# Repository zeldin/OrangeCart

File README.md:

The Orange Cartridge -- an FPGA cartridge for the C64/C128
==========================================================

This is an open source hardware FPGA cartridge for the C64 and C128.
The main features are:
 * ECP5 FPGA with 24k LUTs and 126 KB of block RAM
 * 16 MB of HyperRAM
 * 16 MB of SPI NOR Flash
 * Full speed USB
 * Micro SD-card
 * RGB LED
 * Pushbutton

Usage
-----

For full usage instructions and other detailed information, please refer to
[the wiki][wiki].

The cartridge can be powered from the expansion port, from the USB connector,
or both at once (back-current protection diodes are present at each power
input).

To enter the bootloader, keep the pushbutton pressed down when applying
power.  The LED will start flashing in a rainbow pattern.  A new bitstream
can now be uploaded using DFU.

Example bitstreams
------------------

- [RVCop64](https://github.com/zeldin/RVCop64)
- [super-reu](https://github.com/zeldin/super-reu)

[wiki]: https://github.com/zeldin/OrangeCart/wiki

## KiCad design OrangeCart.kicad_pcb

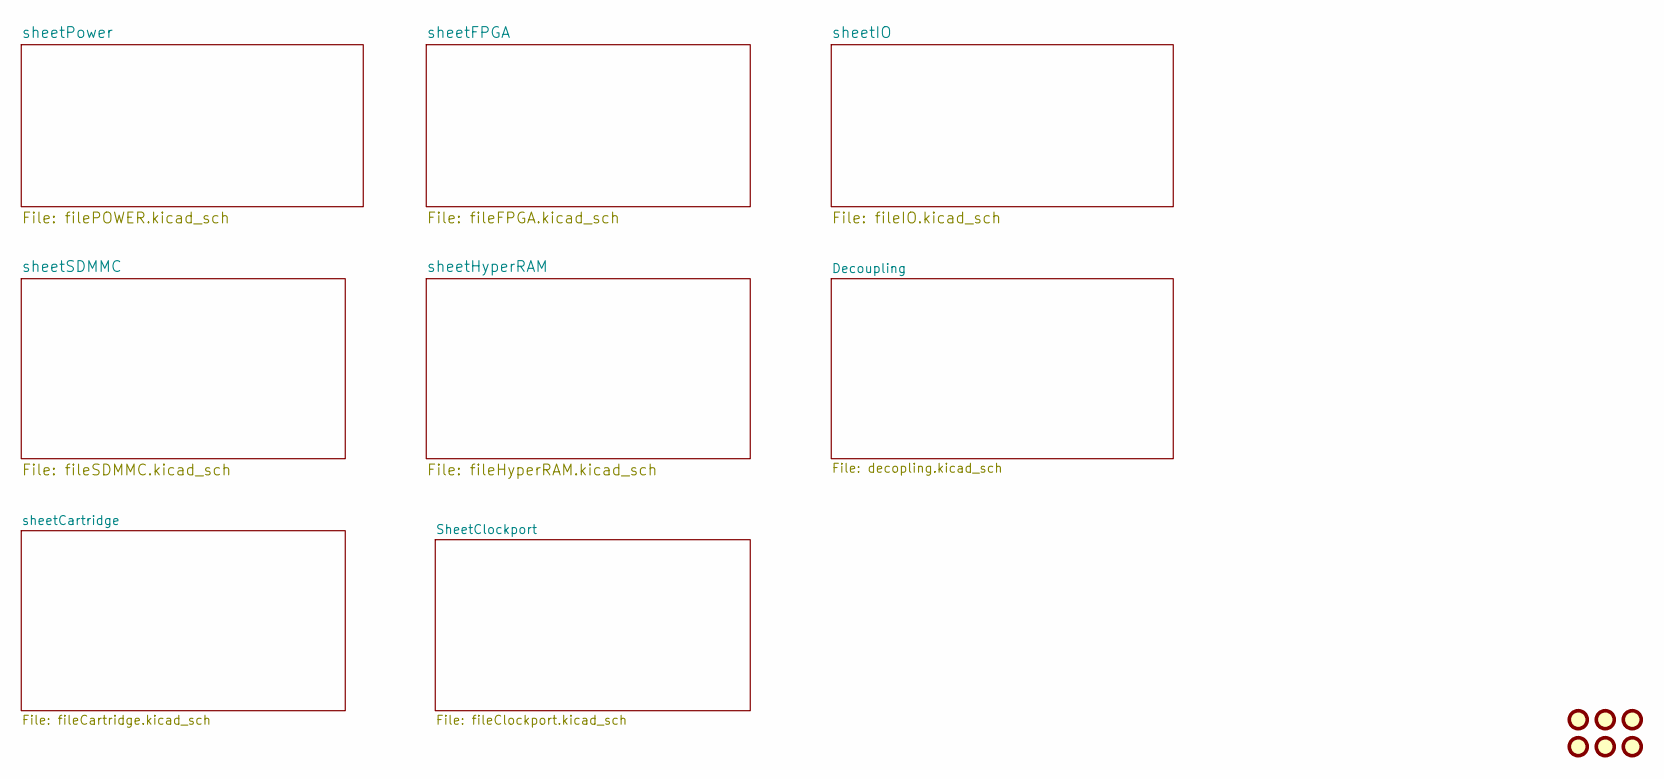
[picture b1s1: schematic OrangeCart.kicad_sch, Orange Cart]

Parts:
FID1, FID2, FID3, FID4, FID5, FID6: Fiducial; Fiducial_0.75mm_Mask1.5mm

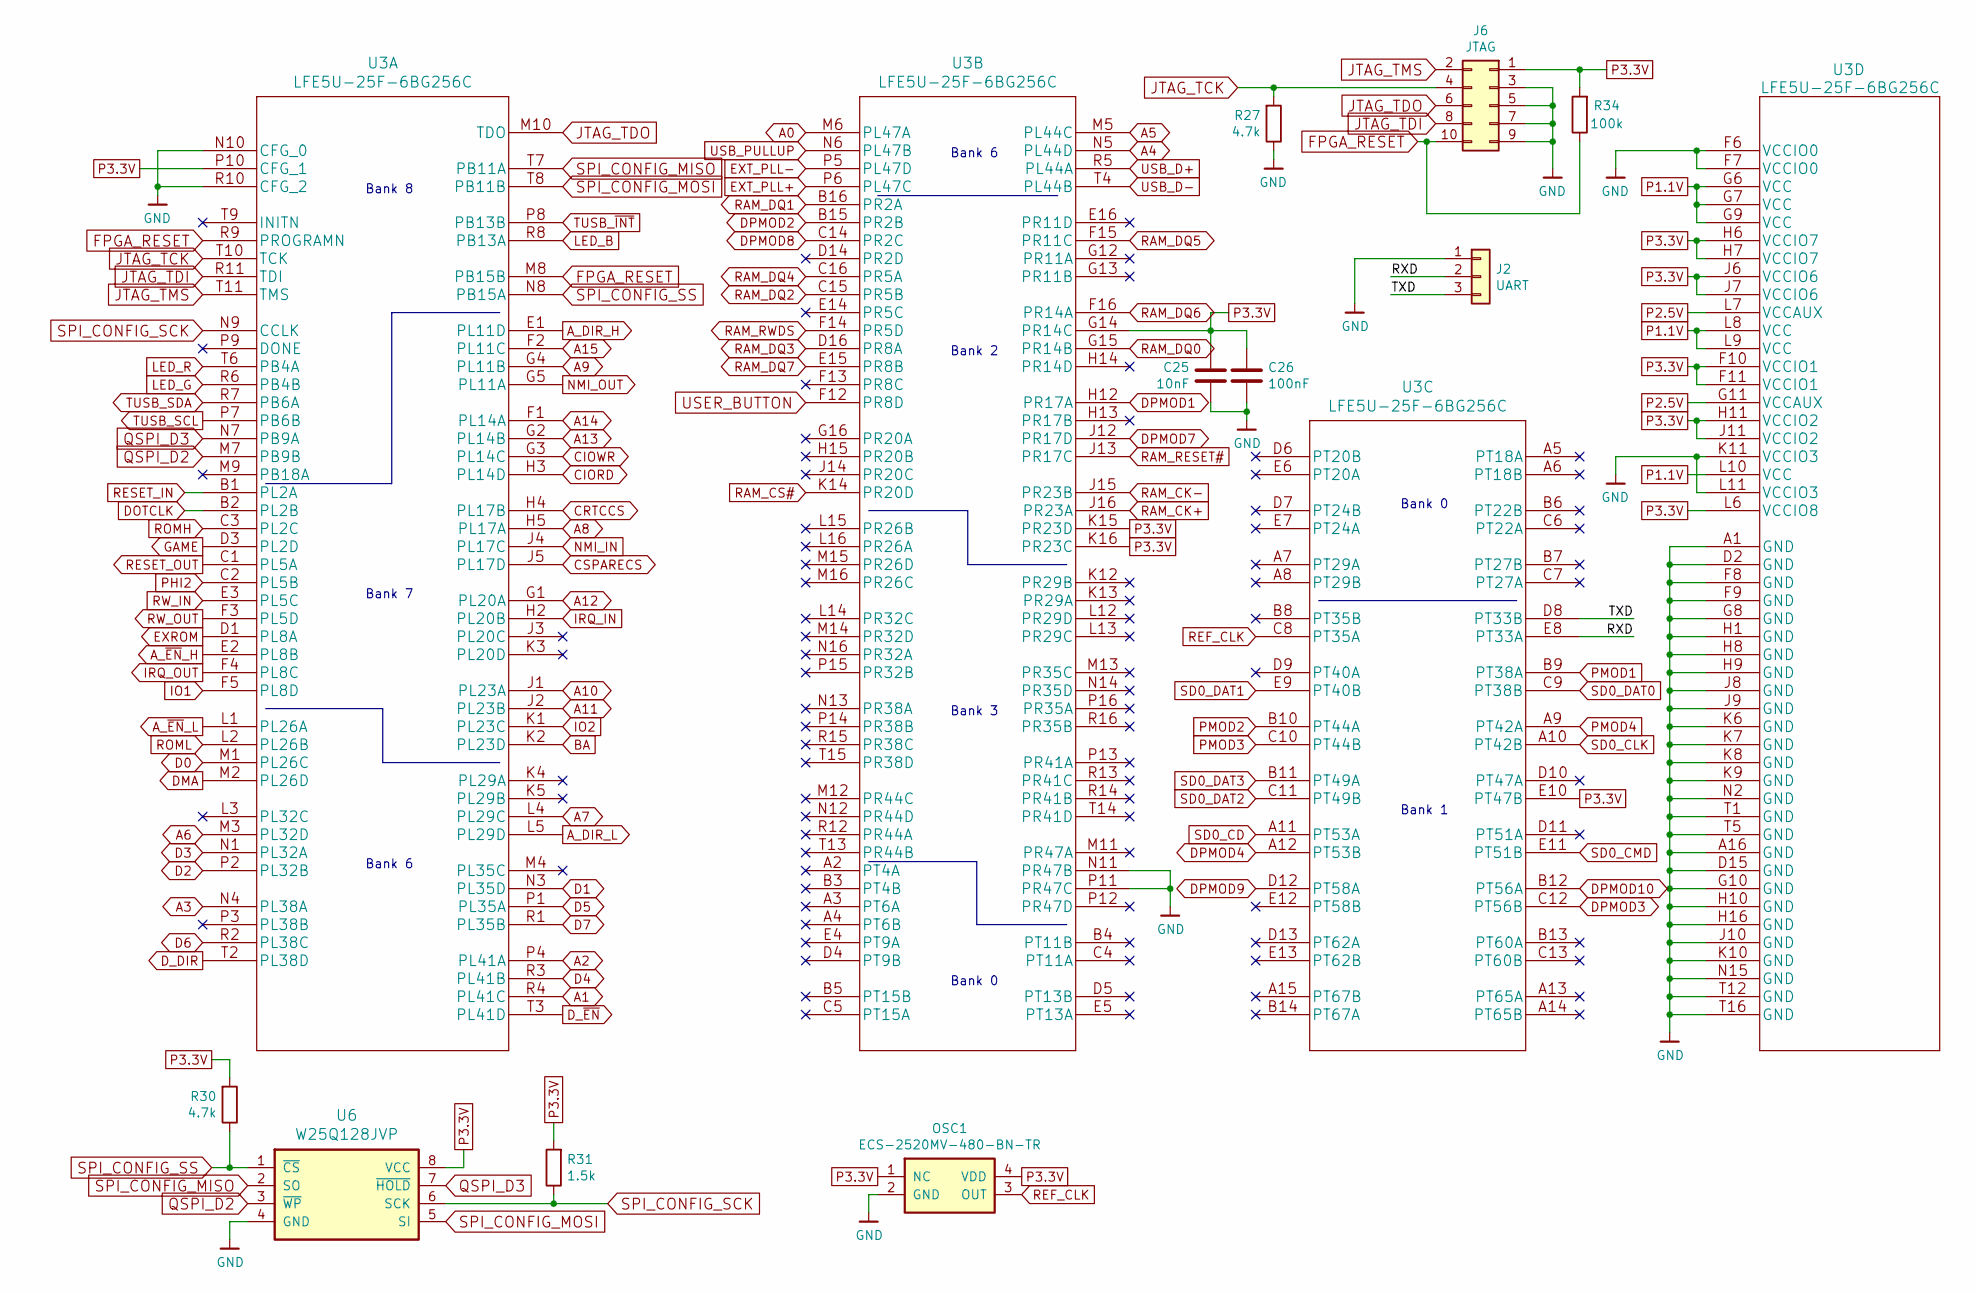
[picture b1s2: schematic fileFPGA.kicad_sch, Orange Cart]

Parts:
C25: 10nF; C_0201_0603Metric; Mouser Part No 187-CL03B103KP3NNNC
C26: 100nF; C_0201_0603Metric; Mouser Part No 187-CL03A104KQ3NNNC
J2: UART; PinHeader_1x03_P1.27mm_Vertical_SMD_Pin1Right; Mouser Part No 855-M50-3630342
J6: JTAG; FTSH-105-XX-X-DV; Mouser Part No 200-FTS10502LDVP
OSC1: ECS-2520MV-480-BN-TR; Oscillator_SMD_ECS_2520MV-xxx-xx-4Pin_2.5x2.0mm; Mouser Part No 520-2520MV-480-BN-T
R27, R30: 4.7k; R_0201_0603Metric; Mouser Part No 603-RC0201FR-074K7L
R31: 1.5k; R_0201_0603Metric; Mouser Part No 603-RC0201FR-071K5L / 667-ERJ-1GNF1501C
R34: 100k; R_0201_0603Metric; Mouser Part No 603-RC0201FR-07100KL / 667-ERJ-1GNF1003C
U3: LFE5U-25F-6BG256C; LFE5U-25F-8BG256C; Mouser Part No 842-LFE5U25F6BG256C
U6: W25Q128JVP; WSON-8-1EP_6x5mm_P1.27mm_EP3.4x4mm; Mouser Part No 454-W25Q128JVPIQTR

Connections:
/sheetFPGA/RXD: J2.2, U3.E8 (PT33A)
/sheetFPGA/TXD: J2.3, U3.D8 (PT33B)
A0: U3.M6 (PL47A); also elsewhere on the board
A1: U3.R4 (PL41C); also elsewhere on the board
A2: U3.P4 (PL41A); also elsewhere on the board
A3: U3.N4 (PL38A); also elsewhere on the board
A4: U3.N5 (PL44D); also elsewhere on the board
A5: U3.M5 (PL44C); also elsewhere on the board
A6: U3.M3 (PL32D); also elsewhere on the board
A7: U3.L4 (PL29C); also elsewhere on the board
A8: U3.H5 (PL17A); also elsewhere on the board
A9: U3.G4 (PL11B); also elsewhere on the board
A10: U3.J1 (PL23A); also elsewhere on the board
A11: U3.J2 (PL23B); also elsewhere on the board
A12: U3.G1 (PL20A); also elsewhere on the board
A13: U3.G2 (PL14B); also elsewhere on the board
A14: U3.F1 (PL14A); also elsewhere on the board
A15: U3.F2 (PL11C); also elsewhere on the board
A_DIR_H: U3.E1 (PL11D); also elsewhere on the board
A_DIR_L: U3.L5 (PL29D); also elsewhere on the board
A_~EN_H: U3.E2 (PL8B); also elsewhere on the board
A_~EN_L: U3.L1 (PL26A); also elsewhere on the board
BA: U3.K2 (PL23D); also elsewhere on the board
CIORD: U3.H3 (PL14D); also elsewhere on the board
CIOWR: U3.G3 (PL14C); also elsewhere on the board
CRTCCS: U3.H4 (PL17B); also elsewhere on the board
CSPARECS: U3.J5 (PL17D); also elsewhere on the board
D0: U3.M1 (PL26C); also elsewhere on the board
D1: U3.N3 (PL35D); also elsewhere on the board
D2: U3.P2 (PL32B); also elsewhere on the board
D3: U3.N1 (PL32A); also elsewhere on the board
D4: U3.R3 (PL41B); also elsewhere on the board
D5: U3.P1 (PL35A); also elsewhere on the board
D6: U3.R2 (PL38C); also elsewhere on the board
D7: U3.R1 (PL35B); also elsewhere on the board
DMA: U3.M2 (PL26D); also elsewhere on the board
DOTCLK: U3.B2 (PL2B); also elsewhere on the board
DPMOD1: U3.H12 (PR17A); also elsewhere on the board
DPMOD2: U3.B15 (PR2B); also elsewhere on the board
DPMOD3: U3.C12 (PT56B); also elsewhere on the board
DPMOD4: U3.A12 (PT53B); also elsewhere on the board
DPMOD7: U3.J12 (PR17D); also elsewhere on the board
DPMOD8: U3.C14 (PR2C); also elsewhere on the board
DPMOD9: U3.D12 (PT58A); also elsewhere on the board
DPMOD10: U3.B12 (PT56A); also elsewhere on the board
D_DIR: U3.T2 (PL38D); also elsewhere on the board
D_~EN: U3.T3 (PL41D); also elsewhere on the board
EXROM: U3.D1 (PL8A); also elsewhere on the board
EXT_PLL+: U3.P6 (PL47C); also elsewhere on the board
EXT_PLL-: U3.P5 (PL47D); also elsewhere on the board
FPGA_RESET: J6.10, R34.1, U3.M8 (PB15B), U3.R9 (PROGRAMN)
GAME: U3.D3 (PL2D); also elsewhere on the board
GND: C25.2, C26.2, J2.1, J6.3, J6.5, J6.7, J6.9, OSC1.2 (GND), R27.1, U3.A1 (GND), U3.A16 (GND), U3.D2 (GND), U3.D15 (GND), U3.F6 (VCCIO0), U3.F7 (VCCIO0), U3.F8 (GND), U3.F9 (GND), U3.G8 (GND), U3.G10 (GND), U3.H1 (GND), U3.H8 (GND), U3.H9 (GND), U3.H10 (GND), U3.H16 (GND), U3.J8 (GND), U3.J9 (GND), U3.J10 (GND), U3.K6 (GND), U3.K7 (GND), U3.K8 (GND), U3.K9 (GND), U3.K10 (GND), U3.K11 (VCCIO3), U3.L11 (VCCIO3), U3.N2 (GND), U3.N10 (CFG_0), U3.N11 (PR47B), U3.N15 (GND), U3.P11 (PR47C), U3.R10 (CFG_2), U3.T1 (GND), U3.T5 (GND), U3.T12 (GND), U3.T16 (GND), U6.4 (GND); also elsewhere on the board
IO1: U3.F5 (PL8D); also elsewhere on the board
IO2: U3.K1 (PL23C); also elsewhere on the board
IRQ_IN: U3.H2 (PL20B); also elsewhere on the board
IRQ_OUT: U3.F4 (PL8C); also elsewhere on the board
JTAG_TCK: J6.4, R27.2, U3.T10 (TCK)
JTAG_TDI: J6.8, U3.R11 (TDI)
JTAG_TDO: J6.6, U3.M10 (TDO)
JTAG_TMS: J6.2, U3.T11 (TMS)
LED_B: U3.R8 (PB13A); also elsewhere on the board
LED_G: U3.R6 (PB4B); also elsewhere on the board
LED_R: U3.T6 (PB4A); also elsewhere on the board
NMI_IN: U3.J4 (PL17C); also elsewhere on the board
NMI_OUT: U3.G5 (PL11A); also elsewhere on the board
P1.1V: U3.G6 (VCC), U3.G7 (VCC), U3.G9 (VCC), U3.L8 (VCC), U3.L9 (VCC), U3.L10 (VCC); also elsewhere on the board
P2.5V: U3.G11 (VCCAUX), U3.L7 (VCCAUX); also elsewhere on the board
P3.3V: C25.1, C26.1, J6.1, OSC1.1 (NC), OSC1.4 (VDD), R30.2, R31.2, R34.2, U3.E10 (PT47B), U3.F10 (VCCIO1), U3.F11 (VCCIO1), U3.G14 (PR14C), U3.H6 (VCCIO7), U3.H7 (VCCIO7), U3.H11 (VCCIO2), U3.J6 (VCCIO6), U3.J7 (VCCIO6), U3.J11 (VCCIO2), U3.K15 (PR23D), U3.K16 (PR23C), U3.L6 (VCCIO8), U3.P10 (CFG_1), U6.8 (VCC); also elsewhere on the board
PHI2: U3.C2 (PL5B); also elsewhere on the board
PMOD1: U3.B9 (PT38A); also elsewhere on the board
PMOD2: U3.B10 (PT44A); also elsewhere on the board
PMOD3: U3.C10 (PT44B); also elsewhere on the board
PMOD4: U3.A9 (PT42A); also elsewhere on the board
QSPI_D2: U3.M7 (PB9B), U6.3 (~WP)
QSPI_D3: U3.N7 (PB9A), U6.7 (~HOLD)
RAM_CK+: U3.J16 (PR23A); also elsewhere on the board
RAM_CK-: U3.J15 (PR23B); also elsewhere on the board
RAM_CS#: U3.K14 (PR20D); also elsewhere on the board
RAM_DQ0: U3.G15 (PR14B); also elsewhere on the board
RAM_DQ1: U3.B16 (PR2A); also elsewhere on the board
RAM_DQ2: U3.C15 (PR5B); also elsewhere on the board
RAM_DQ3: U3.D16 (PR8A); also elsewhere on the board
RAM_DQ4: U3.C16 (PR5A); also elsewhere on the board
RAM_DQ5: U3.F15 (PR11C); also elsewhere on the board
RAM_DQ6: U3.F16 (PR14A); also elsewhere on the board
RAM_DQ7: U3.E15 (PR8B); also elsewhere on the board
RAM_RESET#: U3.J13 (PR17C); also elsewhere on the board
RAM_RWDS: U3.F14 (PR5D); also elsewhere on the board
REF_CLK: OSC1.3 (OUT), U3.C8 (PT35A)
RESET_IN: U3.B1 (PL2A); also elsewhere on the board
RESET_OUT: U3.C1 (PL5A); also elsewhere on the board
ROMH: U3.C3 (PL2C); also elsewhere on the board
ROML: U3.L2 (PL26B); also elsewhere on the board
RW_IN: U3.E3 (PL5C); also elsewhere on the board
RW_OUT: U3.F3 (PL5D); also elsewhere on the board
SD0_CD: U3.A11 (PT53A); also elsewhere on the board
SD0_CLK: U3.A10 (PT42B); also elsewhere on the board
SD0_CMD: U3.E11 (PT51B); also elsewhere on the board
SD0_DAT0: U3.C9 (PT38B); also elsewhere on the board
SD0_DAT1: U3.E9 (PT40B); also elsewhere on the board
SD0_DAT2: U3.C11 (PT49B); also elsewhere on the board
SD0_DAT3: U3.B11 (PT49A); also elsewhere on the board
SPI_CONFIG_MISO: U3.T7 (PB11A), U6.2 (SO)
SPI_CONFIG_MOSI: U3.T8 (PB11B), U6.5 (SI)
SPI_CONFIG_SCK: R31.1, U3.N9 (CCLK), U6.6 (SCK)
SPI_CONFIG_SS: R30.1, U3.N8 (PB15A), U6.1 (~CS)
TUSB_SCL: U3.P7 (PB6B); also elsewhere on the board
TUSB_SDA: U3.R7 (PB6A); also elsewhere on the board
TUSB_~INT: U3.P8 (PB13B); also elsewhere on the board
USB_D+: U3.R5 (PL44A); also elsewhere on the board
USB_D-: U3.T4 (PL44B); also elsewhere on the board
USB_PULLUP: U3.N6 (PL47B); also elsewhere on the board
USER_BUTTON: U3.F12 (PR8D); also elsewhere on the board

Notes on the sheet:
Bank 6
Bank 7
Bank 1
Bank 8
Bank 0
Bank 3
Bank 2

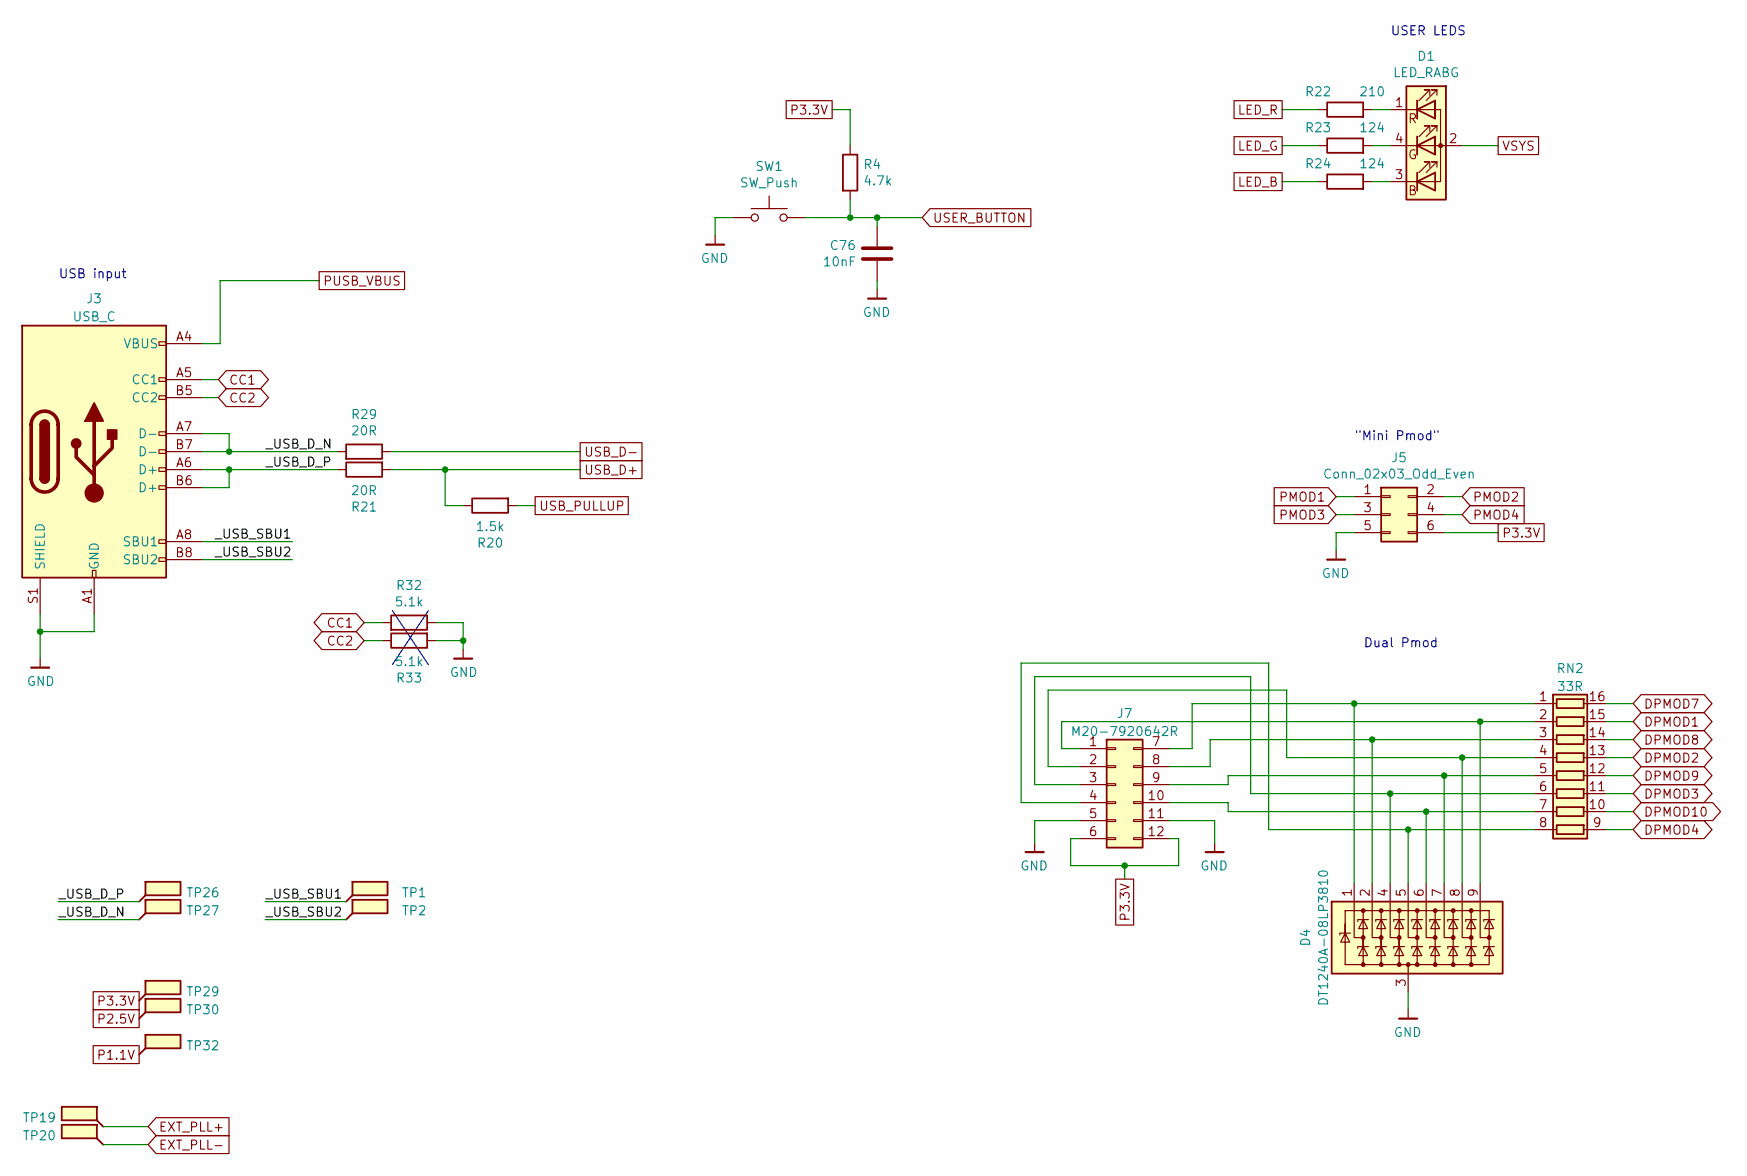
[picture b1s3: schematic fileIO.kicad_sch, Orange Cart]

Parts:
C76: 10nF; C_0201_0603Metric; Mouser Part No 187-CL03B103KP3NNNC
D1: LED_RABG; LED_D5.0mm-4_RGB; Mouser Part No 604-WP154A43VBDZGWCA
D4: DT1240A-08LP3810; UDFN-9_1.0x3.8mm_P0.5mm; Mouser Part No 621-DT1240A08LP38107
J3: USB_C; USB_C_Receptacle_HRO_TYPE-C-31-M-12; Mouser Part No 640-USB4105-GF-A-120
J5: Conn_02x03_Odd_Even; PinSocket_2x03_P2.54mm_Vertical
J7: M20-7920642R; M207920642R; Mouser Part No 855-M20-7920642R
R4: 4.7k; R_0201_0603Metric; Mouser Part No 603-RC0201FR-074K7L
R20: 1.5k; R_0201_0603Metric; Mouser Part No 603-RC0201FR-071K5L / 667-ERJ-1GNF1501C
R21, R29: 20R; R_0201_0603Metric; Mouser Part No 603-RC0201FR-0720RL
R22: 210; R_0402_1005Metric; Mouser Part No 667-ERJ-2RKF2100X
R23, R24: 124; R_0402_1005Metric; Mouser Part No 667-ERJ-2RKF1240X
R32, R33: 5.1k; R_0201_0603Metric; Mouser Part No 603-RC0201JR-075K1L
RN2: 33R; R_Array_Convex_8x0602; Mouser Part No 667-EXB-2HV330JV
SW1: SW_Push; TPB11CGPC004; Mouser Part No 506-TPB11CGPC004
TP1, TP2, TP19, TP20, TP26, TP27, TP29, TP30, TP32: SMD_TP; TestPoint_Pad_D0.5mm

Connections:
/sheetIO/_USB_D_N: J3.A7 (D-), J3.B7 (D-), R29.2, TP27.1
/sheetIO/_USB_D_P: J3.A6 (D+), J3.B6 (D+), R21.1, TP26.1
/sheetIO/_USB_SBU1: J3.A8 (SBU1), TP1.1
/sheetIO/_USB_SBU2: J3.B8 (SBU2), TP2.1
CC1: J3.A5 (CC1), R32.2; also elsewhere on the board
CC2: J3.B5 (CC2), R33.1; also elsewhere on the board
DPMOD1: RN2.15 (R2.2); also elsewhere on the board
DPMOD2: RN2.13 (R4.2); also elsewhere on the board
DPMOD3: RN2.11 (R6.2); also elsewhere on the board
DPMOD4: RN2.9 (R8.2); also elsewhere on the board
DPMOD7: RN2.16 (R1.2); also elsewhere on the board
DPMOD8: RN2.14 (R3.2); also elsewhere on the board
DPMOD9: RN2.12 (R5.2); also elsewhere on the board
DPMOD10: RN2.10 (R7.2); also elsewhere on the board
EXT_PLL+: TP19.1; also elsewhere on the board
EXT_PLL-: TP20.1; also elsewhere on the board
GND: C76.2, D4.3 (A), J3.A1 (GND), J3.A12 (GND), J3.B1 (GND), J3.B12 (GND), J3.S1 (SHIELD), J5.5, J7.5, J7.11, R32.1, R33.2, SW1.1; also elsewhere on the board
LED_B: R24.1; also elsewhere on the board
LED_G: R23.1; also elsewhere on the board
LED_R: R22.1; also elsewhere on the board
unnamed: D1.3 (BK), R24.2
unnamed: D1.4 (GK), R23.2
unnamed: D1.1 (RK), R22.2
unnamed: D4.1 (K1), J7.7, RN2.1 (R1.1)
unnamed: D4.2 (K2), J7.8, RN2.3 (R3.1)
unnamed: D4.4 (K3), J7.3, RN2.6 (R6.1)
unnamed: D4.5 (K4), J7.4, RN2.8 (R8.1)
unnamed: D4.6 (K5), J7.10, RN2.7 (R7.1)
unnamed: D4.7 (K6), J7.9, RN2.5 (R5.1)
unnamed: D4.8 (K7), J7.2, RN2.4 (R4.1)
unnamed: D4.9 (K8), J7.1, RN2.2 (R2.1)
P1.1V: TP32.1; also elsewhere on the board
P2.5V: TP30.1; also elsewhere on the board
P3.3V: J5.6, J7.6, J7.12, R4.1, TP29.1; also elsewhere on the board
PMOD1: J5.1; also elsewhere on the board
PMOD2: J5.2; also elsewhere on the board
PMOD3: J5.3; also elsewhere on the board
PMOD4: J5.4; also elsewhere on the board
PUSB_VBUS: J3.A4 (VBUS), J3.A9 (VBUS), J3.B4 (VBUS), J3.B9 (VBUS); also elsewhere on the board
USB_D+: R20.1, R21.2; also elsewhere on the board
USB_D-: R29.1; also elsewhere on the board
USB_PULLUP: R20.2; also elsewhere on the board
USER_BUTTON: C76.1, R4.2, SW1.2; also elsewhere on the board
VSYS: D1.2 (A); also elsewhere on the board

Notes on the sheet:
Dual Pmod
USER LEDS
USB input
"Mini Pmod"

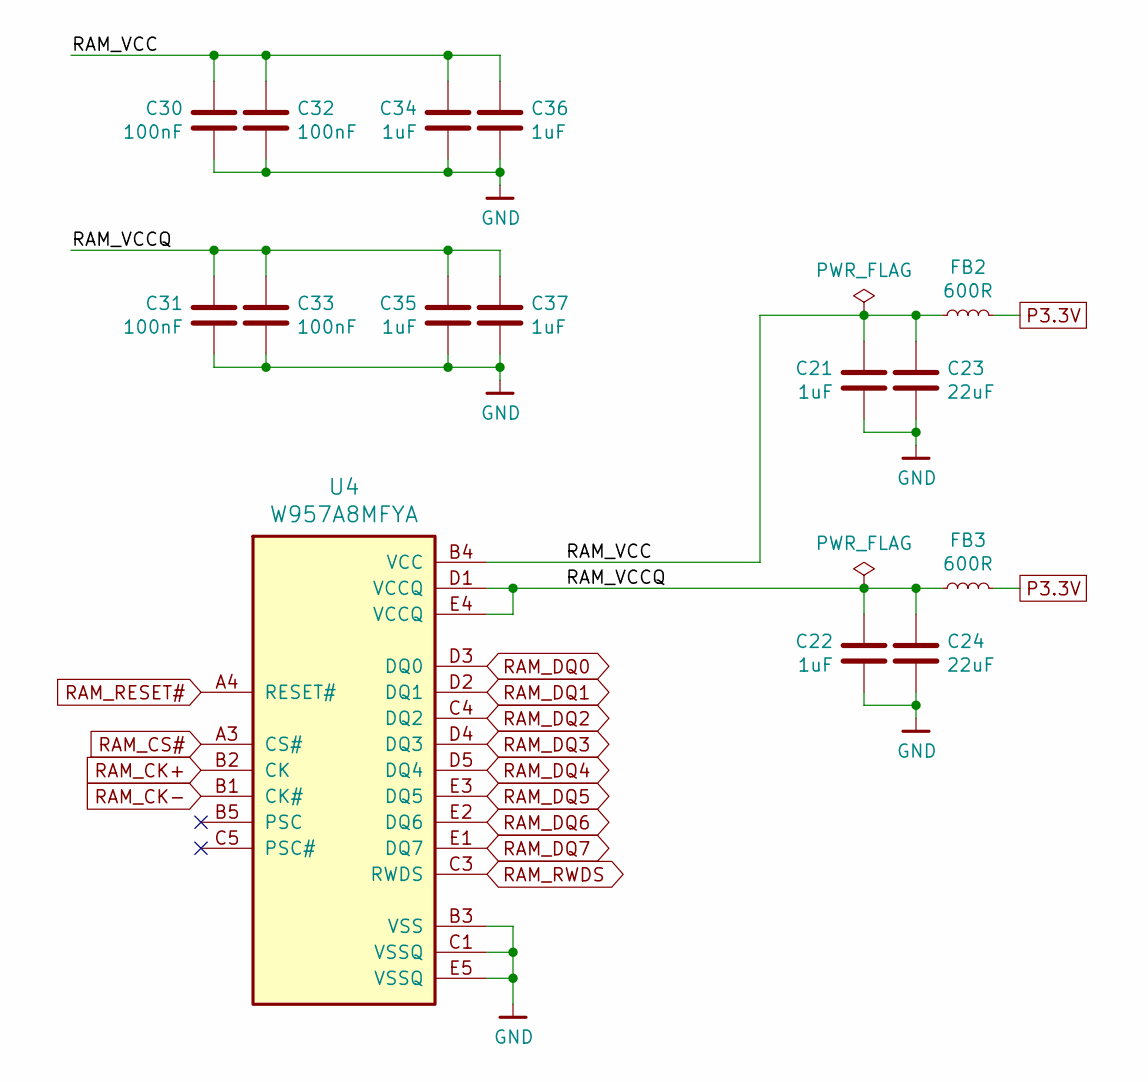
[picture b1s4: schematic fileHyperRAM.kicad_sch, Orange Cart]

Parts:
C21, C22, C34, C35, C36, C37: 1uF; C_0402_1005Metric; Mouser Part No 963-JMK105C6105KV-F
C23, C24: 22uF; C_0603_1608Metric; Mouser Part No 81-GRM188R60J226ME0D / 81-GRM188R60J226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
C30, C31, C32, C33: 100nF; C_0201_0603Metric; Mouser Part No 187-CL03A104KQ3NNNC
FB2, FB3: 600R; L_0402_1005Metric; Mouser Part No 81-BLM15AG601SN1D
U4: W957A8MFYA; T-PBGA-24_6.0x8.0mm_Layout5x5_P1.0mm; Mouser Part No 454-W957A8MFYA5I

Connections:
/sheetHyperRAM/RAM_VCC: C21.1, C23.1, C30.1, C32.1, C34.1, C36.1, FB2.1, U4.B4 (VCC)
/sheetHyperRAM/RAM_VCCQ: C22.1, C24.1, C31.1, C33.1, C35.1, C37.1, FB3.1, U4.D1 (VCCQ), U4.E4 (VCCQ)
GND: C21.2, C22.2, C23.2, C24.2, C30.2, C31.2, C32.2, C33.2, C34.2, C35.2, C36.2, C37.2, U4.B3 (VSS), U4.C1 (VSSQ), U4.E5 (VSSQ); also elsewhere on the board
P3.3V: FB2.2, FB3.2; also elsewhere on the board
RAM_CK+: U4.B2 (CK); also elsewhere on the board
RAM_CK-: U4.B1 (CK#); also elsewhere on the board
RAM_CS#: U4.A3 (CS#); also elsewhere on the board
RAM_DQ0: U4.D3 (DQ0); also elsewhere on the board
RAM_DQ1: U4.D2 (DQ1); also elsewhere on the board
RAM_DQ2: U4.C4 (DQ2); also elsewhere on the board
RAM_DQ3: U4.D4 (DQ3); also elsewhere on the board
RAM_DQ4: U4.D5 (DQ4); also elsewhere on the board
RAM_DQ5: U4.E3 (DQ5); also elsewhere on the board
RAM_DQ6: U4.E2 (DQ6); also elsewhere on the board
RAM_DQ7: U4.E1 (DQ7); also elsewhere on the board
RAM_RESET#: U4.A4 (RESET#); also elsewhere on the board
RAM_RWDS: U4.C3 (RWDS); also elsewhere on the board

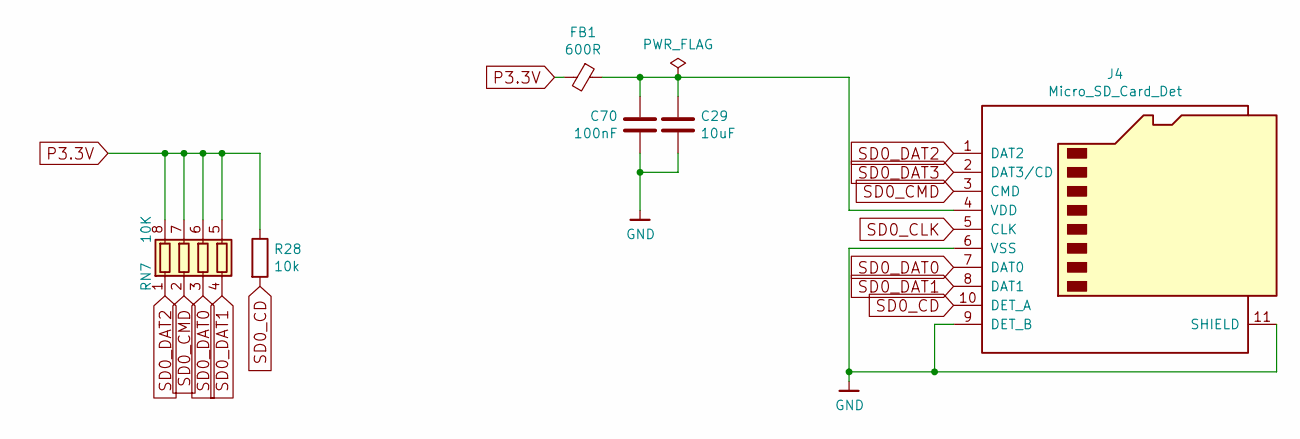
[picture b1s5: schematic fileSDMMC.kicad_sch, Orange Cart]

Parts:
C29: 10uF; C_0402_1005Metric; Mouser Part No 81-GRM155R60J106ME5D
C70: 100nF; C_0201_0603Metric; Mouser Part No 187-CL03A104KQ3NNNC
FB1: 600R; L_0402_1005Metric; Mouser Part No 81-BLM15AG601SN1D
J4: Micro_SD_Card_Det; SDCARD_MOLEX_503398-1892; Mouser Part No 538-503398-1892
R28: 10k; R_0201_0603Metric; Mouser Part No 603-RC0201FR-0710KL
RN7: 10K; R_Array_Convex_4x0402; Mouser Part No 667-EXB-28V103JX

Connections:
GND: C29.1, C70.1, J4.6 (VSS), J4.9 (DET_B), J4.11 (SHIELD); also elsewhere on the board
unnamed: C29.2, C70.2, FB1.1, J4.4 (VDD)
P3.3V: FB1.2, R28.1, RN7.5 (R4.2), RN7.6 (R3.2), RN7.7 (R2.2), RN7.8 (R1.2); also elsewhere on the board
SD0_CD: J4.10 (DET_A), R28.2; also elsewhere on the board
SD0_CLK: J4.5 (CLK); also elsewhere on the board
SD0_CMD: J4.3 (CMD), RN7.2 (R2.1); also elsewhere on the board
SD0_DAT0: J4.7 (DAT0), RN7.3 (R3.1); also elsewhere on the board
SD0_DAT1: J4.8 (DAT1), RN7.4 (R4.1); also elsewhere on the board
SD0_DAT2: J4.1 (DAT2), RN7.1 (R1.1); also elsewhere on the board
SD0_DAT3: J4.2 (DAT3/CD); also elsewhere on the board

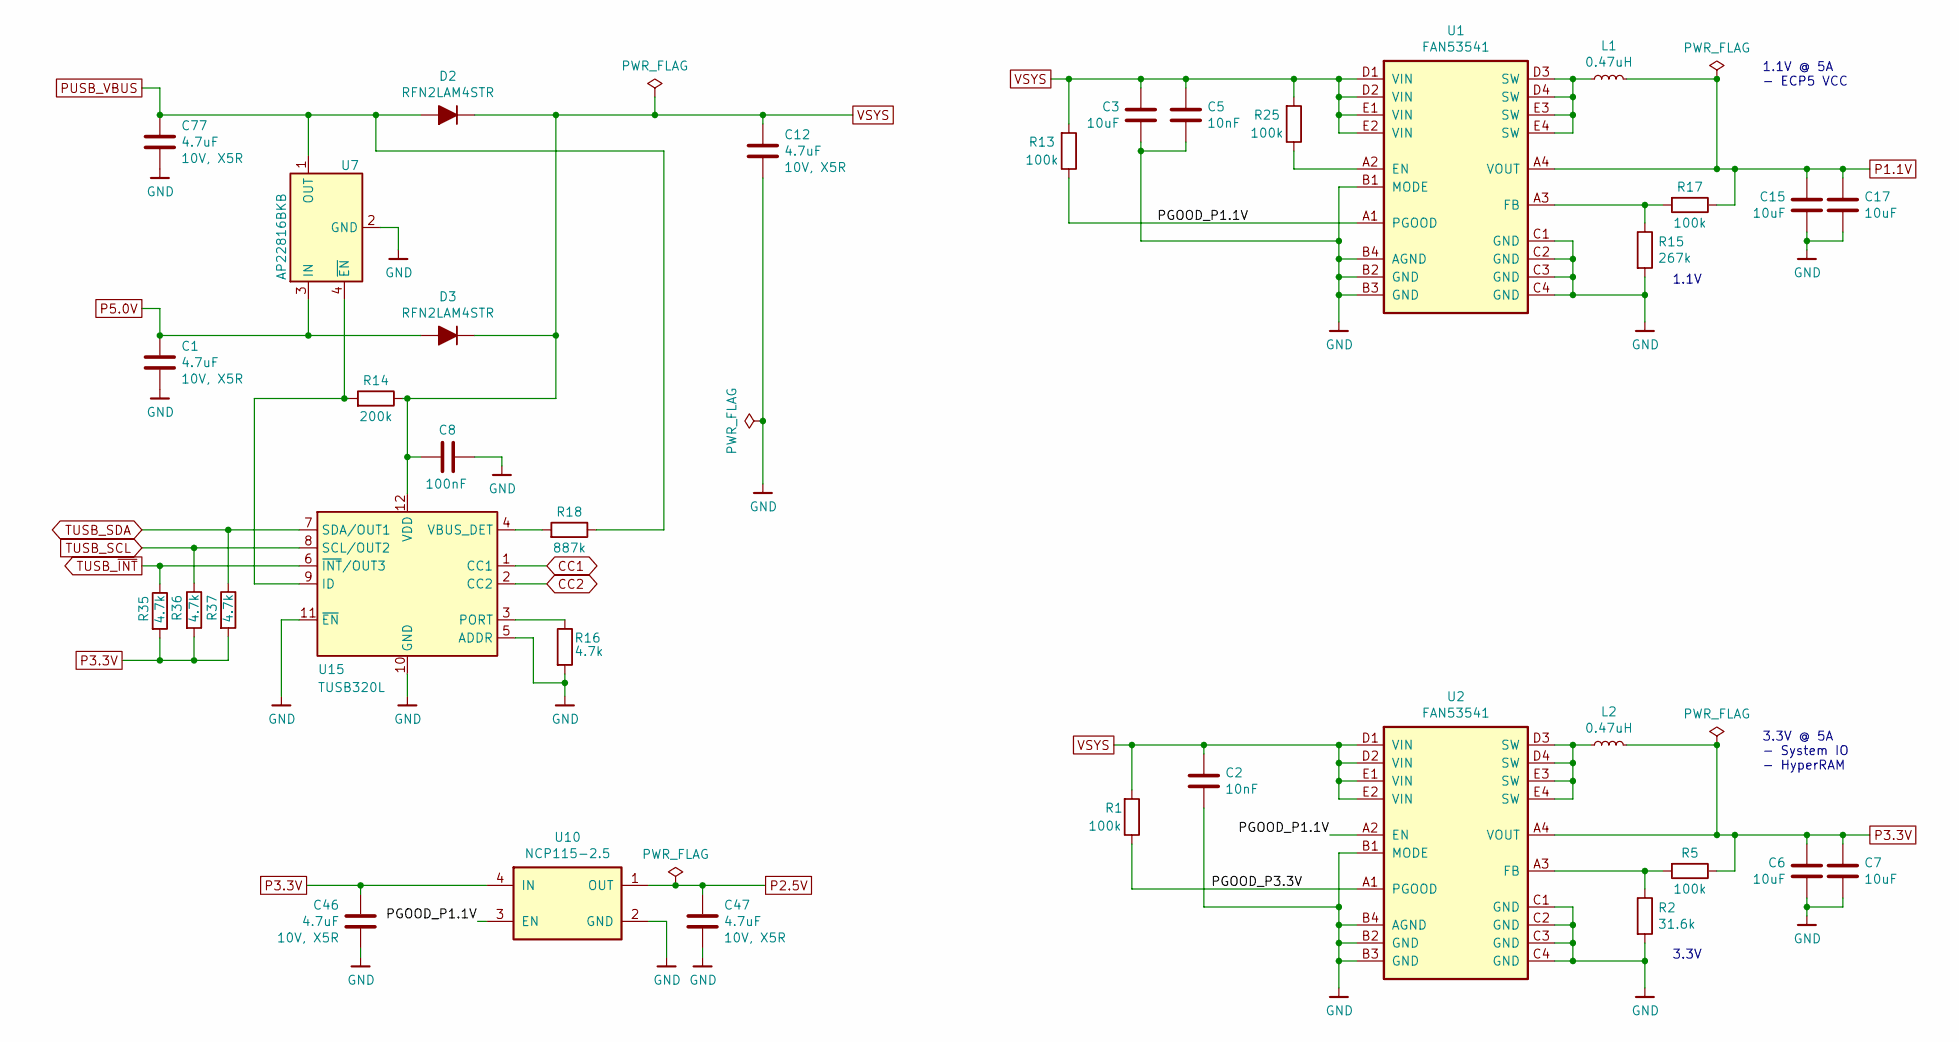
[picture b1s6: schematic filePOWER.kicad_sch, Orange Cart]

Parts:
C1, C12, C46, C47, C77: 4.7uF; C_0402_1005Metric; Mouser Part No 81-GRM155R61A475MEAD / 81-GRM155R61A475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
C2, C5: 10nF; C_0201_0603Metric; Mouser Part No 187-CL03B103KP3NNNC
C3: 10uF; C_0603_1608Metric; Mouser Part No 963-LMK107BBJ106MALT
C6, C7, C15, C17: 10uF; C_0402_1005Metric; Mouser Part No 81-GRM155R60J106ME5D
C8: 100nF; C_0201_0603Metric; Mouser Part No 187-CL03A104KQ3NNNC
D2, D3: RFN2LAM4STR; D_SOD-128; Mouser Part No 755-RFN2LAM4STR
L1, L2: 0.47uH; L_0805_2012Metric; Mouser Part No 187-CIGT201210UHR47M
R1, R5, R13, R17, R25: 100k; R_0201_0603Metric; Mouser Part No 603-RC0201FR-07100KL / 667-ERJ-1GNF1003C
R2: 31.6k; R_0201_0603Metric; Mouser Part No 603-RC0201FR-0731K6L
R14: 200k; R_0201_0603Metric; Mouser Part No 603-RC0201FR-07200KL
R15: 267k; R_0201_0603Metric; Mouser Part No 603-RC0201FR-07267KL / 667-ERJ-1GNF2673C
R16, R35, R36, R37: 4.7k; R_0402_1005Metric; Mouser Part No 603-RC0402JR-074K7L
R18: 887k; R_0201_0603Metric; Mouser Part No 603-RC0201FR-07887KL
U1, U2: FAN53541; WLCSP-20_1.934x2.434mm_Layout4x5_P0.4mm; Mouser Part No 512-FAN53541UCX
U7: AP22816BKB; SOT-23-5; Mouser Part No 621-AP22816BKBWT-7
U10: NCP115-2.5; Texas_X2SON-4_1x1mm_P0.65mm; Mouser Part No 863-NCP115CMX250TCG
U15: TUSB320L; Texas_X2QFN-12_1.6x1.6mm_P0.4mm; Mouser Part No 595-TUSB320LAIRWBR

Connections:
/sheetPower/PGOOD_P1.1V: R13.1, U1.A1 (PGOOD), U2.A2 (EN), U10.3 (EN)
/sheetPower/PGOOD_P3.3V: R1.1, U2.A1 (PGOOD)
CC1: U15.1 (CC1); also elsewhere on the board
CC2: U15.2 (CC2); also elsewhere on the board
GND: C1.2, C2.1, C3.1, C5.1, C6.1, C7.1, C8.2, C12.2, C15.1, C17.1, C46.2, C47.2, C77.2, R2.2, R15.2, R16.2, U1.B1 (MODE), U1.B2 (GND), U1.B3 (GND), U1.B4 (AGND), U1.C1 (GND), U1.C2 (GND), U1.C3 (GND), U1.C4 (GND), U2.B1 (MODE), U2.B2 (GND), U2.B3 (GND), U2.B4 (AGND), U2.C1 (GND), U2.C2 (GND), U2.C3 (GND), U2.C4 (GND), U7.2 (GND), U10.2 (GND), U15.5 (ADDR), U15.10 (GND), U15.11 (~EN); also elsewhere on the board
unnamed: L1.1, U1.D3 (SW), U1.D4 (SW), U1.E3 (SW), U1.E4 (SW)
unnamed: L2.1, U2.D3 (SW), U2.D4 (SW), U2.E3 (SW), U2.E4 (SW)
unnamed: R25.1, U1.A2 (EN)
unnamed: R15.1, R17.2, U1.A3 (FB)
unnamed: R2.1, R5.2, U2.A3 (FB)
unnamed: R14.2, U7.4 (~EN), U15.9 (ID)
unnamed: R16.1, U15.3 (PORT)
unnamed: R18.2, U15.4 (VBUS_DET)
P1.1V: C15.2, C17.2, L1.2, R17.1, U1.A4 (VOUT); also elsewhere on the board
P2.5V: C47.1, U10.1 (OUT); also elsewhere on the board
P3.3V: C6.2, C7.2, C46.1, L2.2, R5.1, R35.2, R36.2, R37.2, U2.A4 (VOUT), U10.4 (IN); also elsewhere on the board
P5.0V: C1.1, D3.2 (A), U7.3 (IN); also elsewhere on the board
PUSB_VBUS: C77.1, D2.2 (A), R18.1, U7.1 (OUT), U7.5 (OUT); also elsewhere on the board
TUSB_SCL: R36.1, U15.8 (SCL/OUT2); also elsewhere on the board
TUSB_SDA: R37.1, U15.7 (SDA/OUT1); also elsewhere on the board
TUSB_~INT: R35.1, U15.6 (~INT/OUT3); also elsewhere on the board
VSYS: C2.2, C3.2, C5.2, C8.1, C12.1, D2.1 (K), D3.1 (K), R1.2, R13.2, R14.1, R25.2, U1.D1 (VIN), U1.D2 (VIN), U1.E1 (VIN), U1.E2 (VIN), U2.D1 (VIN), U2.D2 (VIN), U2.E1 (VIN), U2.E2 (VIN), U15.12 (VDD); also elsewhere on the board

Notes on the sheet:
1.1V @ 5A - ECP5 VCC
1.1V
3.3V @ 5A - System IO - HyperRAM
3.3V

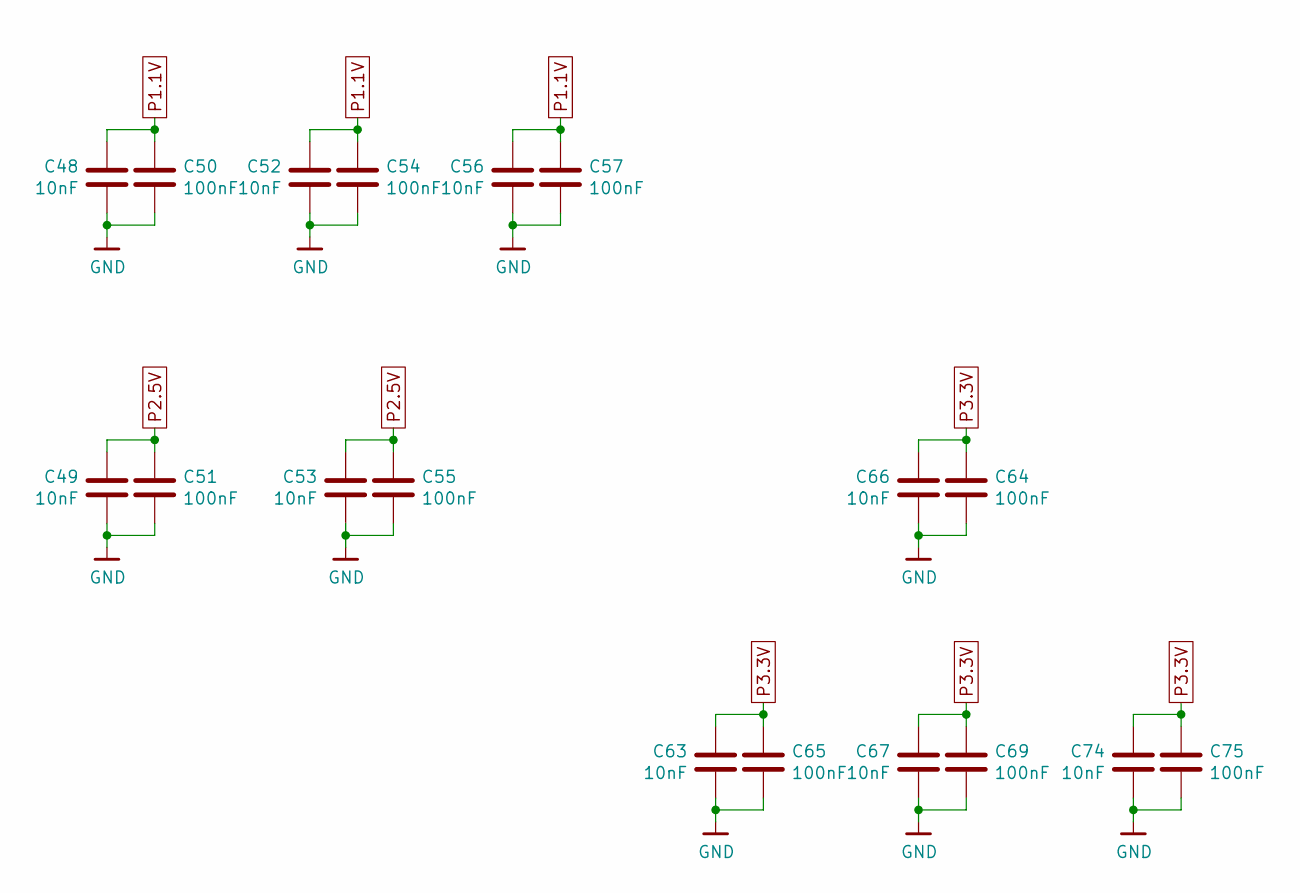
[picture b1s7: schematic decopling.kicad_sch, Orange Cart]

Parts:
C48, C49, C52, C53, C56, C63, C66, C67, C74: 10nF; C_0201_0603Metric; Mouser Part No 187-CL03B103KP3NNNC
C50, C51, C54, C55, C57, C64, C65, C69, C75: 100nF; C_0201_0603Metric; Mouser Part No 187-CL03A104KQ3NNNC

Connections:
GND: C48.2, C49.2, C50.2, C51.2, C52.2, C53.2, C54.2, C55.2, C56.2, C57.2, C63.2, C64.2, C65.2, C66.2, C67.2, C69.2, C74.2, C75.2; also elsewhere on the board
P1.1V: C48.1, C50.1, C52.1, C54.1, C56.1, C57.1; also elsewhere on the board
P2.5V: C49.1, C51.1, C53.1, C55.1; also elsewhere on the board
P3.3V: C63.1, C64.1, C65.1, C66.1, C67.1, C69.1, C74.1, C75.1; also elsewhere on the board

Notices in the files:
OrangeCart.kicad_pcb:
Licensed under CERN OHL v.1.2
